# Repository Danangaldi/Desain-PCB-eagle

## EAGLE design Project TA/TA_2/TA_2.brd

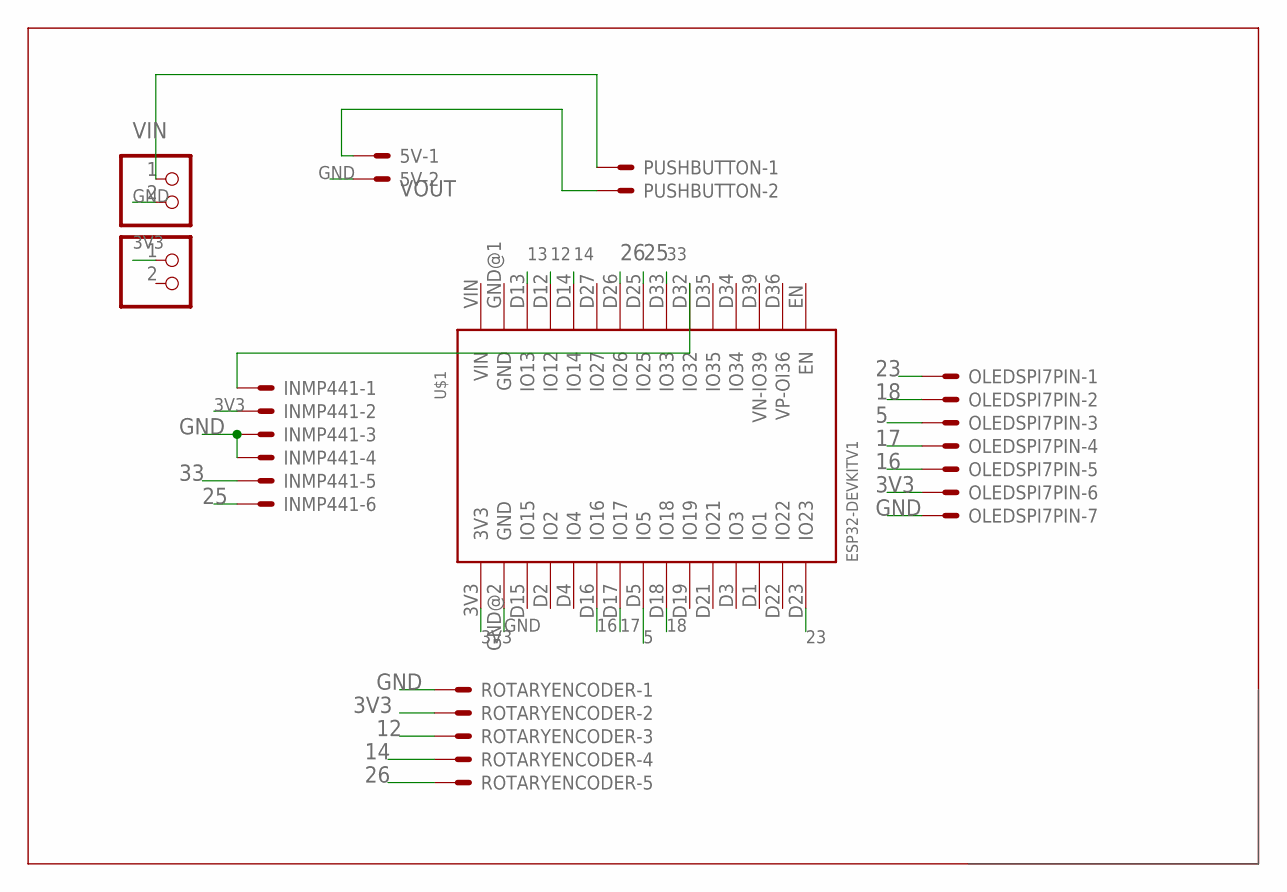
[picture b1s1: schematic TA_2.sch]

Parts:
5V: JST-XH-02-PIN-LONG-PAD; JST-XH-02-PACKAGE-LONG-PAD
INMP441: JST-XH-06-PIN-LONG-PAD; JST-XH-06-PACKAGE-LONG-PAD
OLEDSPI7PIN: JST-XH-07-PIN-LONG-PAD; JST-XH-07-PACKAGE-LONG-PAD
PUSHBUTTON: JST-XH-02-PIN-LONG-PAD; JST-XH-02-PACKAGE-LONG-PAD
ROTARYENCODER: JST-XH-05-PIN-LONG-PAD; JST-XH-05-PACKAGE-LONG-PAD
U$1: ESP32DEVKITV1; ESP32-DEVKITV1
VIN: PINHD-1X2; 1X02
VOUT: PINHD-1X2; 1X02

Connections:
3V3: INMP441.2, OLEDSPI7PIN.6, ROTARYENCODER.2, U$1.3V3, VOUT.1
5: OLEDSPI7PIN.3, U$1.D5 (IO5)
12: ROTARYENCODER.3, U$1.D12 (IO12)
13: U$1.D13 (IO13)
14: ROTARYENCODER.4, U$1.D14 (IO14)
16: OLEDSPI7PIN.5, U$1.D16 (IO16)
17: OLEDSPI7PIN.4, U$1.D17 (IO17)
18: OLEDSPI7PIN.2, U$1.D18 (IO18)
23: OLEDSPI7PIN.1, U$1.D23 (IO23)
25: INMP441.6, U$1.D25 (IO25)
26: ROTARYENCODER.5, U$1.D26 (IO26)
33: INMP441.5, U$1.D33 (IO33)
GND: 5V.2, INMP441.3, INMP441.4, OLEDSPI7PIN.7, ROTARYENCODER.1, U$1.GND@2 (GND), VIN.2
unnamed: PUSHBUTTON.1, VIN.1
unnamed: 5V.1, PUSHBUTTON.2
unnamed: INMP441.1, U$1.D32 (IO32)

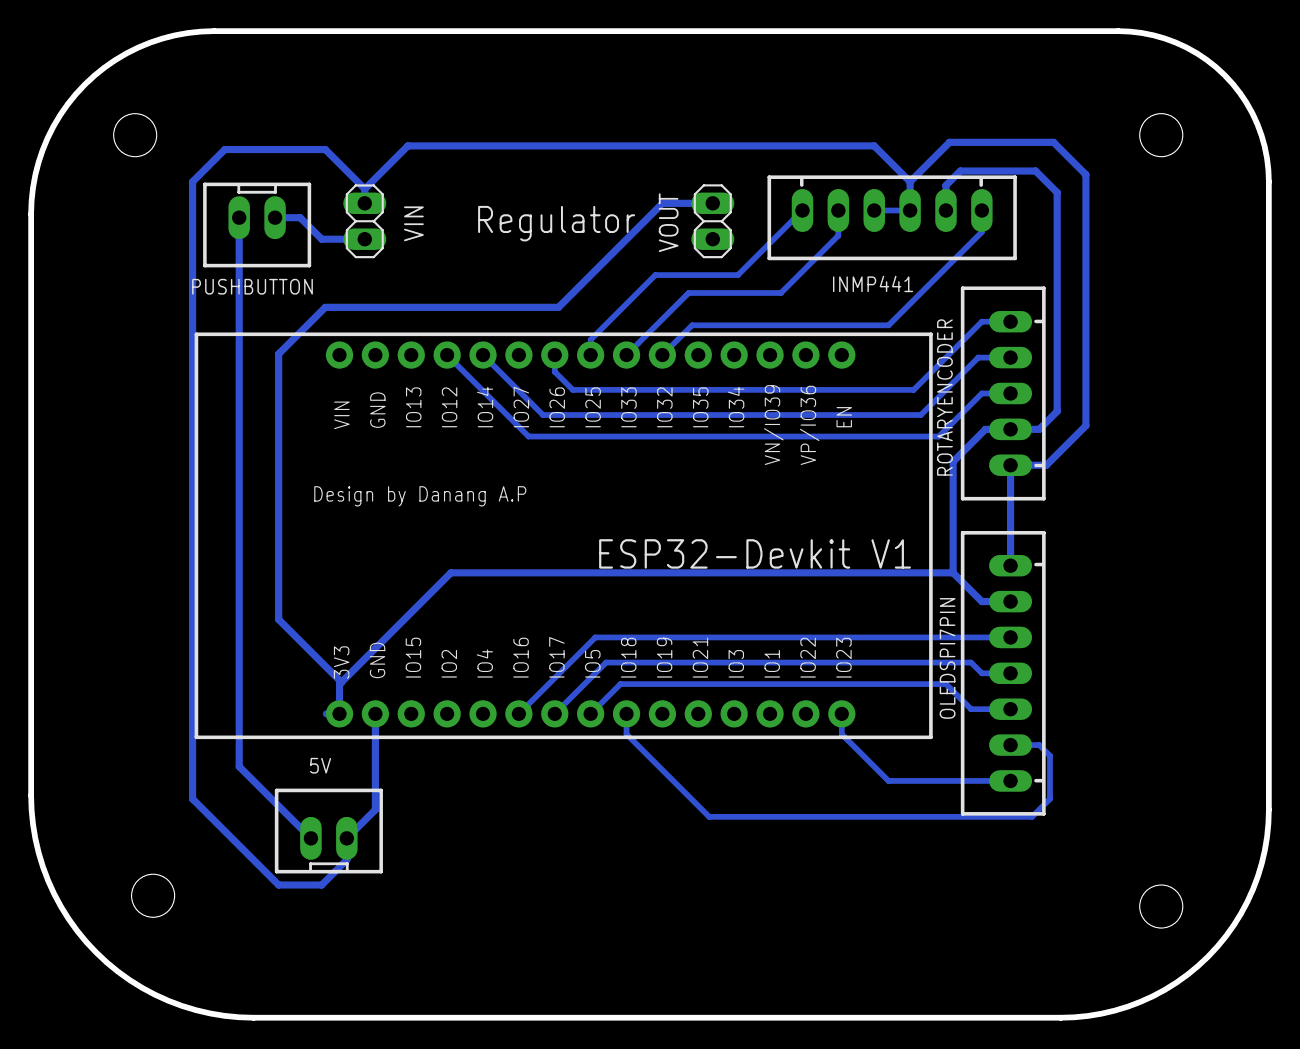
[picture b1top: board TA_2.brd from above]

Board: 2 copper layers, 87.6 x 69.9 mm, 8 parts (0 on the bottom side), 15 nets.

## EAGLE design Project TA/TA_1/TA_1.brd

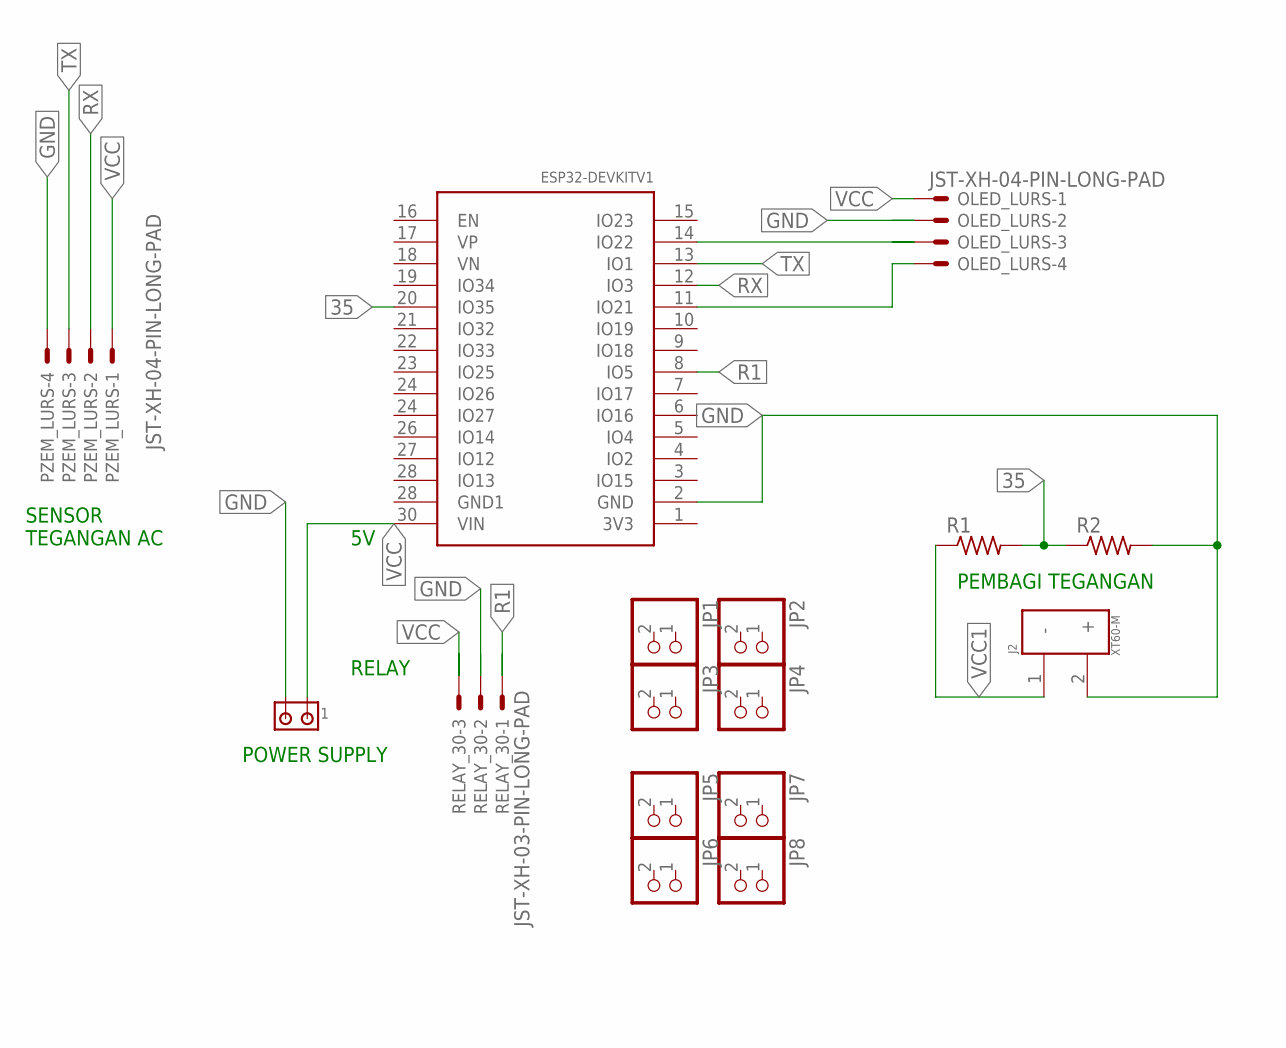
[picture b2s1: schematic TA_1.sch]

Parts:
J1: 350428-1
J2: XT60-M; AMASS_XT60-M
JP1, JP2, JP3, JP4, JP5, JP6, JP7, JP8: PINHD-1X2; 1X02
OLED_LURS: JST-XH-04-PIN-LONG-PAD; JST-XH-04-PACKAGE-LONG-PAD
PZEM_LURS: JST-XH-04-PIN-LONG-PAD; JST-XH-04-PACKAGE-LONG-PAD
R1, R2: R-US_0207/10; 0207/10
RELAY_30: JST-XH-03-PIN-LONG-PAD; JST-XH-03-PACKAGE-LONG-PAD
U$1: ESP32DEVKITV1; ESP32-DEVKITV1

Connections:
35: R1.2, R2.1, U$1.20 (IO35)
GND: J1.2, J2.2 (+), OLED_LURS.2, PZEM_LURS.4, R2.2, RELAY_30.2, U$1.2 (GND)
unnamed: OLED_LURS.4, U$1.11 (IO21)
unnamed: OLED_LURS.3, U$1.14 (IO22)
R1: RELAY_30.1, U$1.8 (IO5)
RX: PZEM_LURS.2, U$1.12 (IO3)
TX: PZEM_LURS.3, U$1.13 (IO1)
VCC: J1.1, OLED_LURS.1, PZEM_LURS.1, RELAY_30.3, U$1.30 (VIN)
VCC1: J2.1 (-), R1.1

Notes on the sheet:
POWER SUPPLY
RELAY
PEMBAGI TEGANGAN
SENSOR TEGANGAN AC

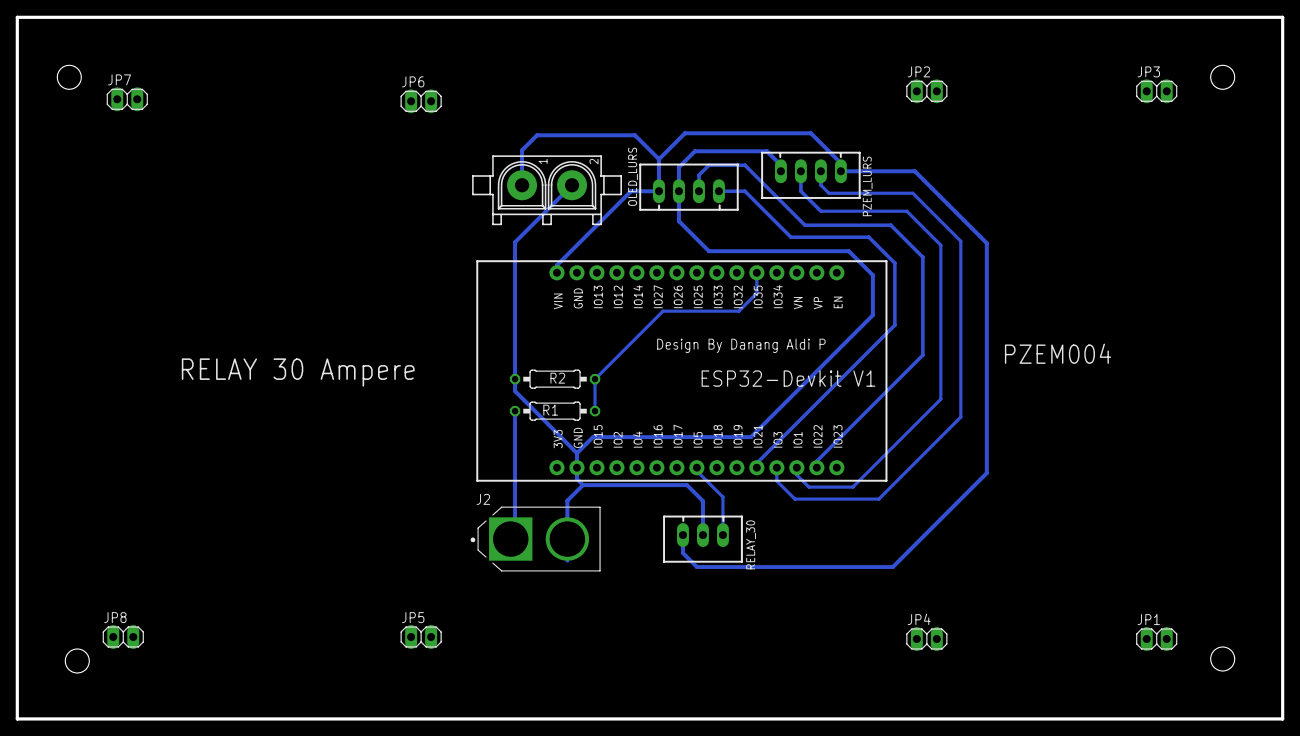
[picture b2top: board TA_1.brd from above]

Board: 2 copper layers, 160.8 x 89.2 mm, 16 parts (0 on the bottom side), 9 nets.

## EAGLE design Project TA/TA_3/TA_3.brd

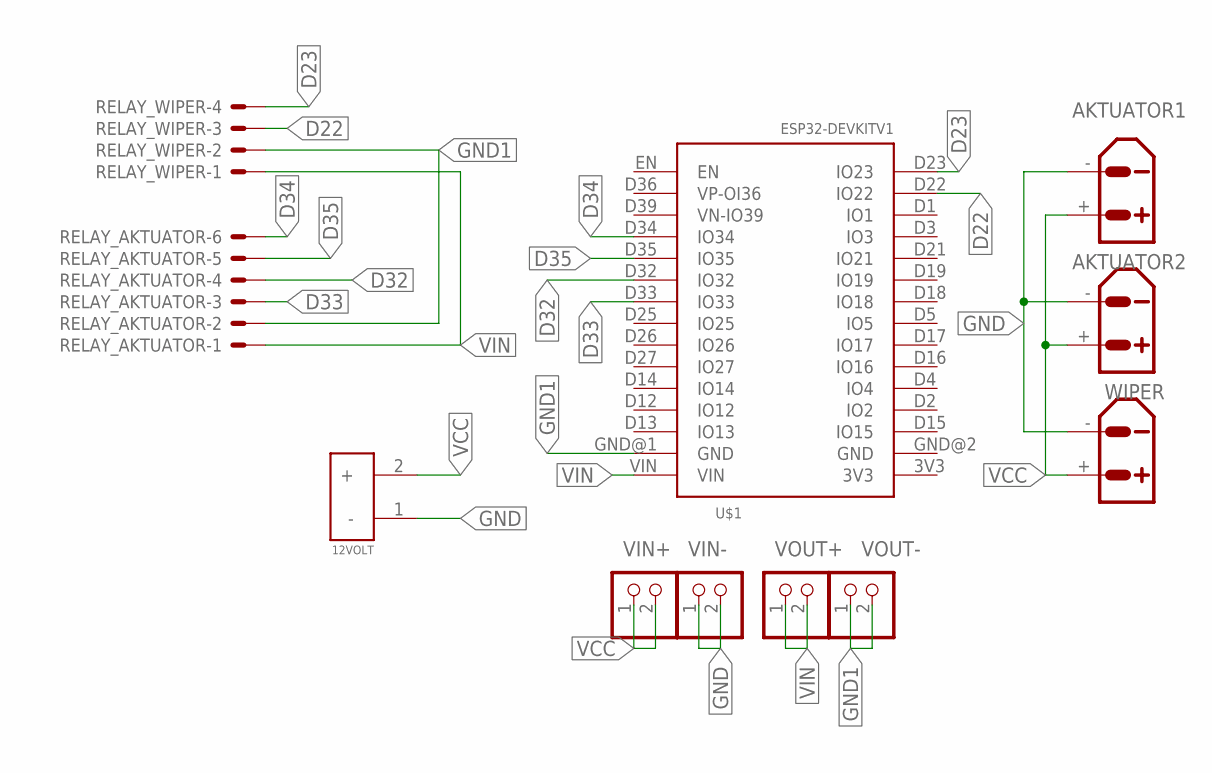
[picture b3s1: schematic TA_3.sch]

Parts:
12VOLT: XT60-M; AMASS_XT60-M
AKTUATOR1, AKTUATOR2: XT30UPB-F
RELAY_AKTUATOR: JST-XH-06-PIN-LONG-PAD; JST-XH-06-PACKAGE-LONG-PAD
RELAY_WIPER: JST-XH-04-PIN-LONG-PAD; JST-XH-04-PACKAGE-LONG-PAD
U$1: ESP32DEVKITV1; ESP32-DEVKITV1
VIN+: PINHD-1X2; 1X02
VIN-: PINHD-1X2; 1X02
VOUT+: PINHD-1X2; 1X02
VOUT-: PINHD-1X2; 1X02
WIPER: XT30UPB-F

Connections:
D22: RELAY_WIPER.3, U$1.D22 (IO22)
D23: RELAY_WIPER.4, U$1.D23 (IO23)
D32: RELAY_AKTUATOR.4, U$1.D32 (IO32)
D33: RELAY_AKTUATOR.3, U$1.D33 (IO33)
D34: RELAY_AKTUATOR.6, U$1.D34 (IO34)
D35: RELAY_AKTUATOR.5, U$1.D35 (IO35)
GND: 12VOLT.1 (-), AKTUATOR1.-, AKTUATOR2.-, VIN-.1, VIN-.2, WIPER.-
GND1: RELAY_AKTUATOR.2, RELAY_WIPER.2, U$1.GND@1 (GND), VOUT-.1, VOUT-.2
VCC: 12VOLT.2 (+), AKTUATOR1.+, AKTUATOR2.+, VIN+.1, VIN+.2, WIPER.+
VIN: RELAY_AKTUATOR.1, RELAY_WIPER.1, U$1.VIN, VOUT+.1, VOUT+.2

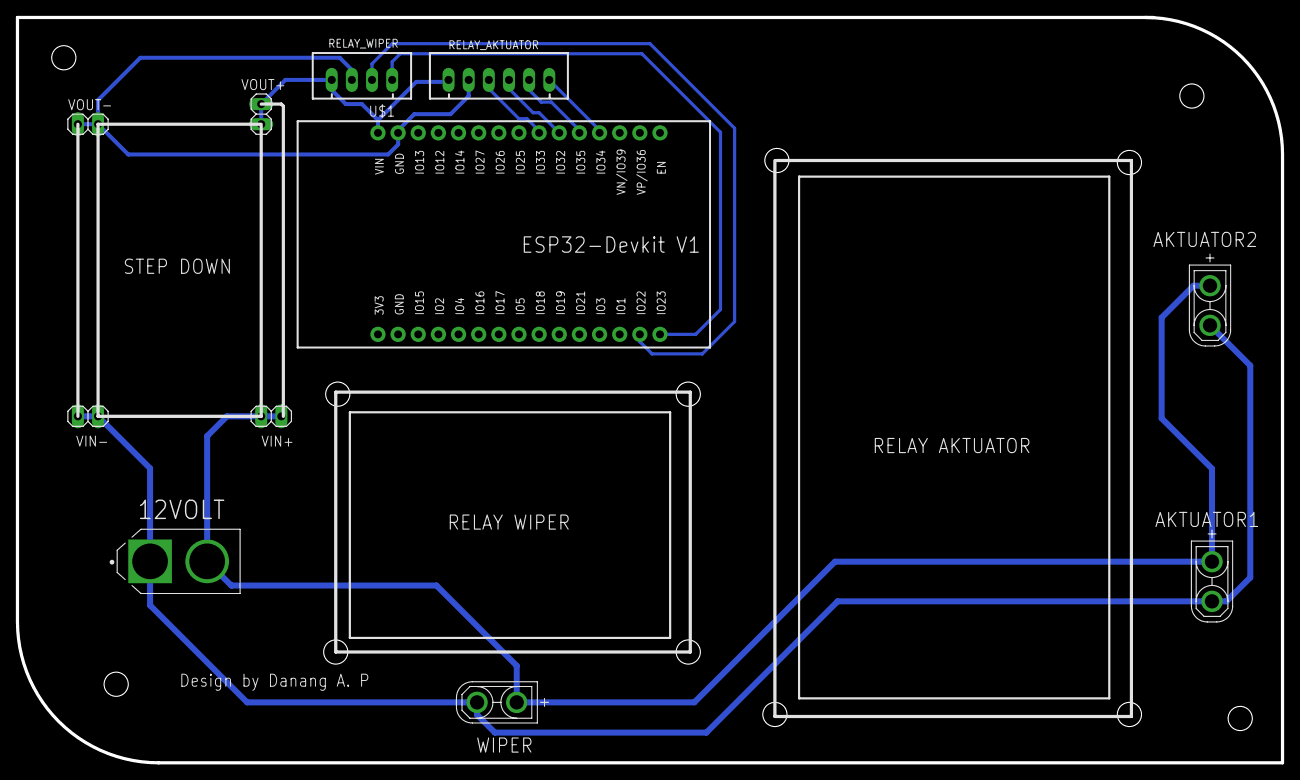
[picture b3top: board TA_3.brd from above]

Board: 2 copper layers, 159.5 x 94.0 mm, 11 parts (0 on the bottom side), 10 nets.

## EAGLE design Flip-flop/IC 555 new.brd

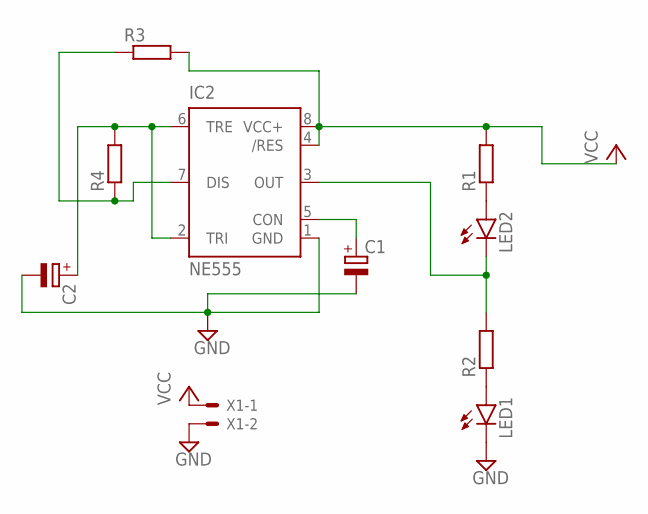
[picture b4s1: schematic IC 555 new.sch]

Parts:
C1, C2: CPOL-EUE2.5-6; E2,5-6
IC2: NE555; DIL-08
LED1, LED2: LED5MM
R1, R2, R3, R4: R-EU_0204/5; 0204/5
X1: JST-XH-02-PIN-ROUND-PAD; JST-XH-02-PACKAGE-ROUND-PAD

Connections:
GND: C1.-, C2.-, IC2.1 (GND), LED1.K (C), X1.2
unnamed: LED1.A, R2.1
unnamed: C2.+, IC2.2 (TRI), IC2.6 (TRE), R4.2
unnamed: IC2.7 (DIS), R3.1, R4.1
unnamed: C1.+, IC2.5 (CON)
unnamed: LED2.A, R1.1
unnamed: IC2.3 (OUT), LED2.K (C), R2.2
VCC: IC2.4 (/RES), IC2.8 (VCC+), R1.2, R3.2, X1.1

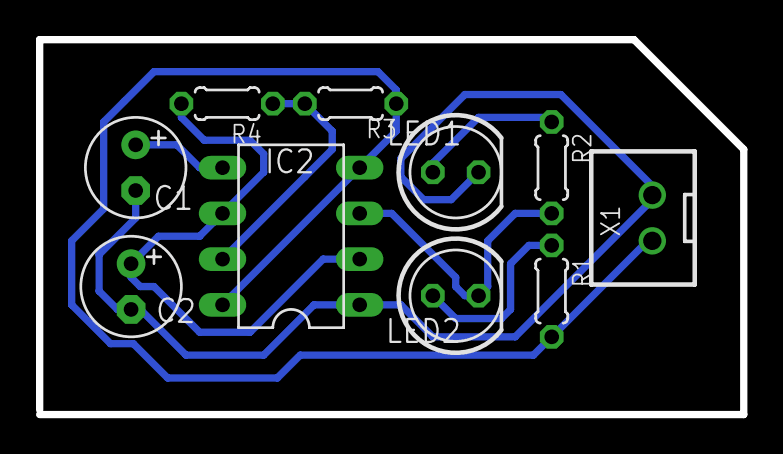
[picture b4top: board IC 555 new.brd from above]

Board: 2 copper layers, 39.1 x 20.8 mm, 10 parts (0 on the bottom side), 8 nets.

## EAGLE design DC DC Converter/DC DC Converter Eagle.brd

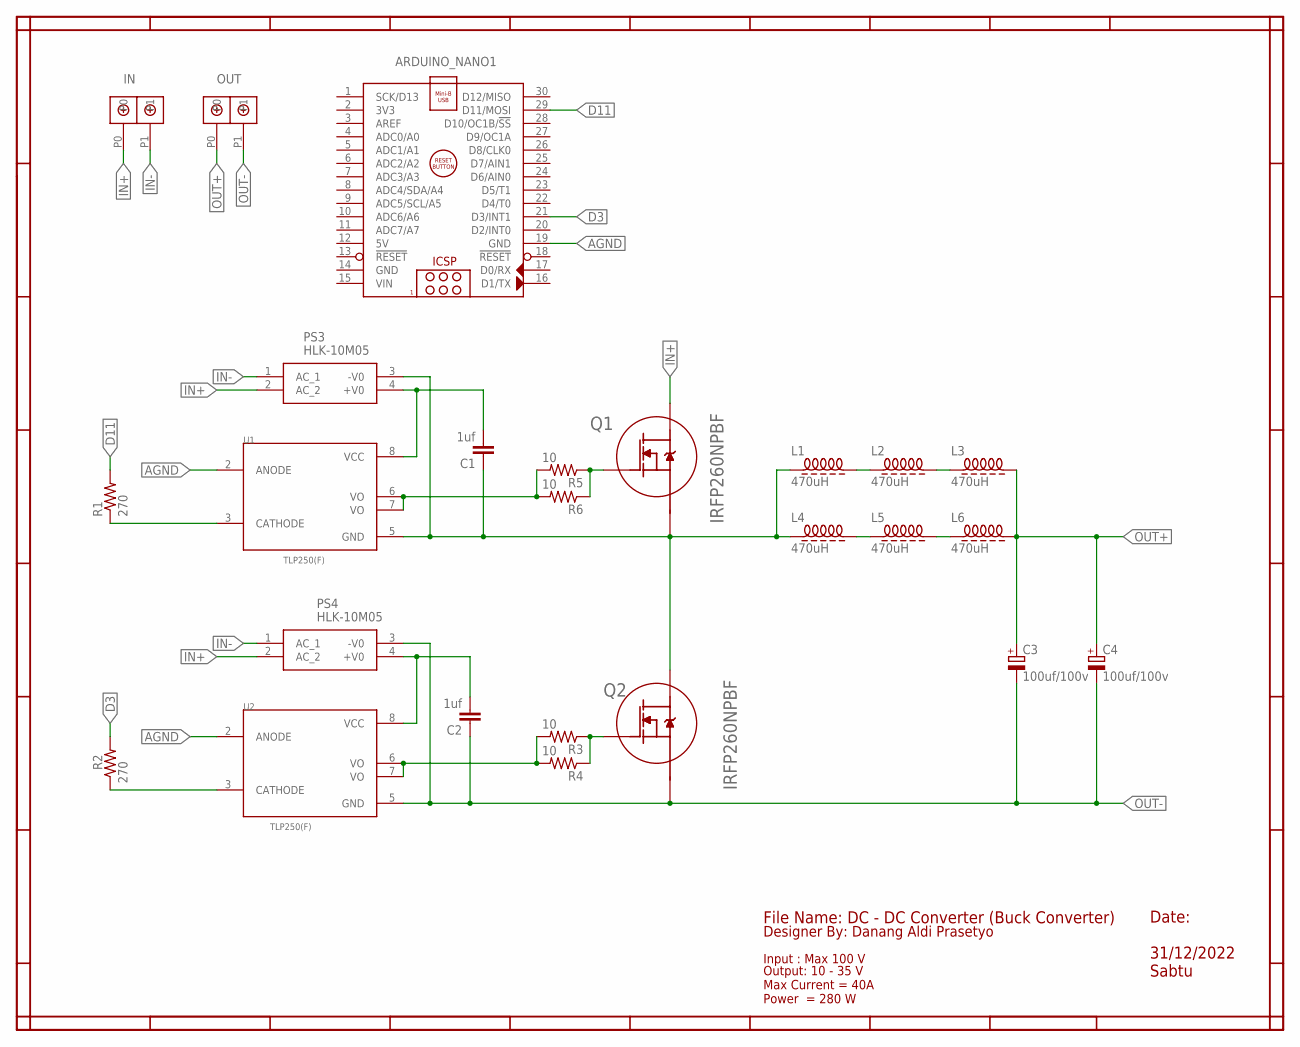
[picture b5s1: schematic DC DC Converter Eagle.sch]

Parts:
ARDUINO_NANO1: ARDUINO_NANO
C1, C2: 1uf; C025-024X044
C3, C4: 100uf/100v; E5-10,5
L1, L2, L3, L4, L5, L6: 470uH; Z15/15
PS3, PS4: HLK-10M05; HLK10M05
Q1, Q2: IRFP260NPBF; TO545P1590X530X2460-3
R1, R2: 270; 0207/7
R3, R4, R5, R6: 10; 0207/7
U1, U2: TLP250(F); DIP1016W50P254L966H380Q8P
U$1, U$2: DBCONN-1X2

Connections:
5V: ARDUINO_NANO1.12 (5V)
AGND: ARDUINO_NANO1.19 (GND), U1.2 (ANODE), U2.2 (ANODE)
D3: ARDUINO_NANO1.21 (D3/INT1), R2.2
D11: ARDUINO_NANO1.29 (D11/MOSI), R1.2
GND: ARDUINO_NANO1.14 (GND)
IN+: PS3.2 (AC_2), PS4.2 (AC_2), Q1.2 (D), U$1.P0
IN-: PS3.1 (AC_1), PS4.1 (AC_1), U$1.P1
unnamed: C1.2, PS3.4 (+V0), U1.8 (VCC)
unnamed: C1.1, L1.1, L4.1, PS3.3 (-V0), Q1.3 (S), Q2.2 (D), U1.5 (GND)
unnamed: R1.1, U1.3 (CATHODE)
unnamed: Q1.1 (G), R5.1, R6.1
unnamed: R5.2, R6.2, U1.6 (VO), U1.7 (VO)
unnamed: R2.1, U2.3 (CATHODE)
unnamed: C2.2, PS4.4 (+V0), U2.8 (VCC)
unnamed: R3.2, R4.2, U2.6 (VO), U2.7 (VO)
unnamed: Q2.1 (G), R3.1, R4.1
unnamed: L1.2, L2.1
unnamed: L2.2, L3.1
unnamed: L4.2, L5.1
unnamed: L5.2, L6.1
OUT+: C3.+, C4.+, L3.2, L6.2, U$2.P0
OUT-: C2.1, C3.-, C4.-, PS4.3 (-V0), Q2.3 (S), U2.5 (GND), U$2.P1
VIN: ARDUINO_NANO1.15 (VIN)

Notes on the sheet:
OUT
File Name: DC - DC Converter (Buck Converter)
Designer By: Danang Aldi Prasetyo
Input : Max 100 V
Output: 10 - 35 V Max Current = 40A Power = 280 W
Date: 31/12/2022 Sabtu

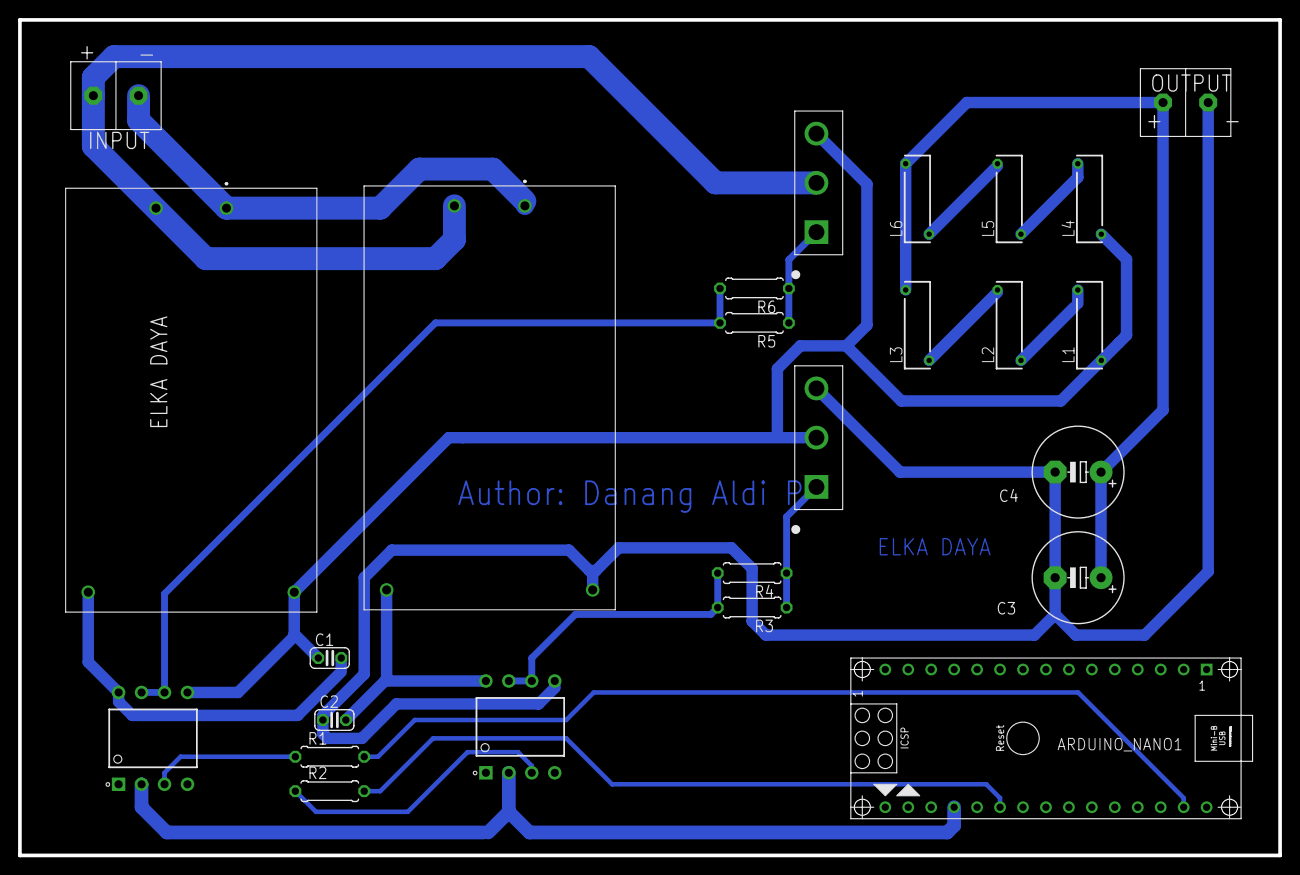
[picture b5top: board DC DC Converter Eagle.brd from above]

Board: 2 copper layers, 139.4 x 92.5 mm, 25 parts (0 on the bottom side), 20 nets.
